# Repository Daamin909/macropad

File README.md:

# Daamin's ShrekPad

### Inspiration

I wanted to boost my productivity and add an aesthetic looking device to my desk setup.

### Challenges

Believe it or not, this was my first time using Fusion 360! I spammed ChatGPT and #hackpad with queries. It also took me a lotta time making the PCB and routing it 😭. I had to reroute a hundred times.

### Case

The case features a very hot Orange and Black look with the keycaps being black and Knob being orange too.

Branding: There is a "Shrek" engraving on both the bottom and middle plate. The top case features an engraving of Shrek's face.

Thickness

- Top: 7mm
- Middle: 1.5mm
- Bottom: 11.5mm
- **Total:** 20mm

### Specifications

BOM:

- 11x Blank DSA Keycaps (11x Black)
- 11x Cherry MX Switches
- 12x 1N4148 diodes
- 1x XIAO RP2040
- 4x M3x20 Bolt ([not available at HQ? if not, then buy from here.](https://amzn.in/d/27J4X2p))
- 4x M3 Nuts
- 4x M3 Heatset
- 1x SSD1306 128x32 0.91" OLED (5V VCC, 3.3V logic, I2C)
- 1x EC11 Rotary Encoder
- 1x Rotary Encoder Knob
- 1x PCB (Please choose "Black" color while ordering 🙃)
- 1x Case (I would like both the TOP and MIDDLE to be printed in Orange and BOTTOM in Black, if not available: Message me @Daamin on Slack)

Others:

- KMK Firmware
- TOP.step
- MIDDLE.step
- BOTTOM.step

|           Schematic            |           PCB            |            Case            |
| :----------------------------: | :----------------------: | :------------------------: |
|  |  |  |

Notes:
Top and Middle printed in Orange, Bottom with Black.
PCB Color has to be black too.

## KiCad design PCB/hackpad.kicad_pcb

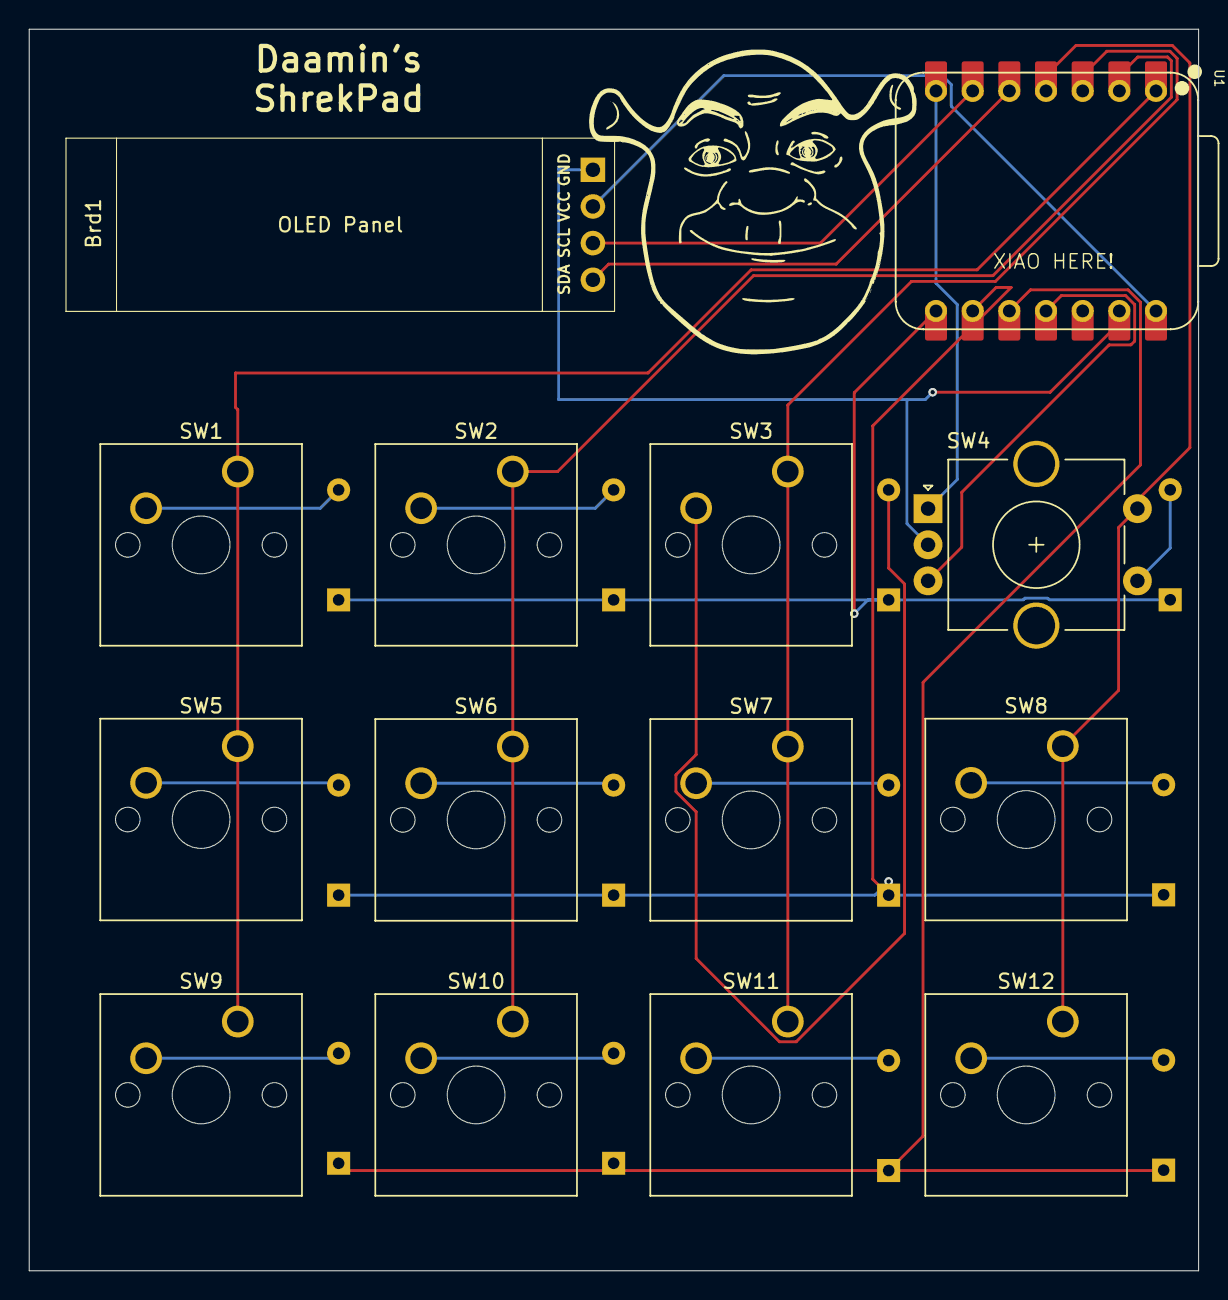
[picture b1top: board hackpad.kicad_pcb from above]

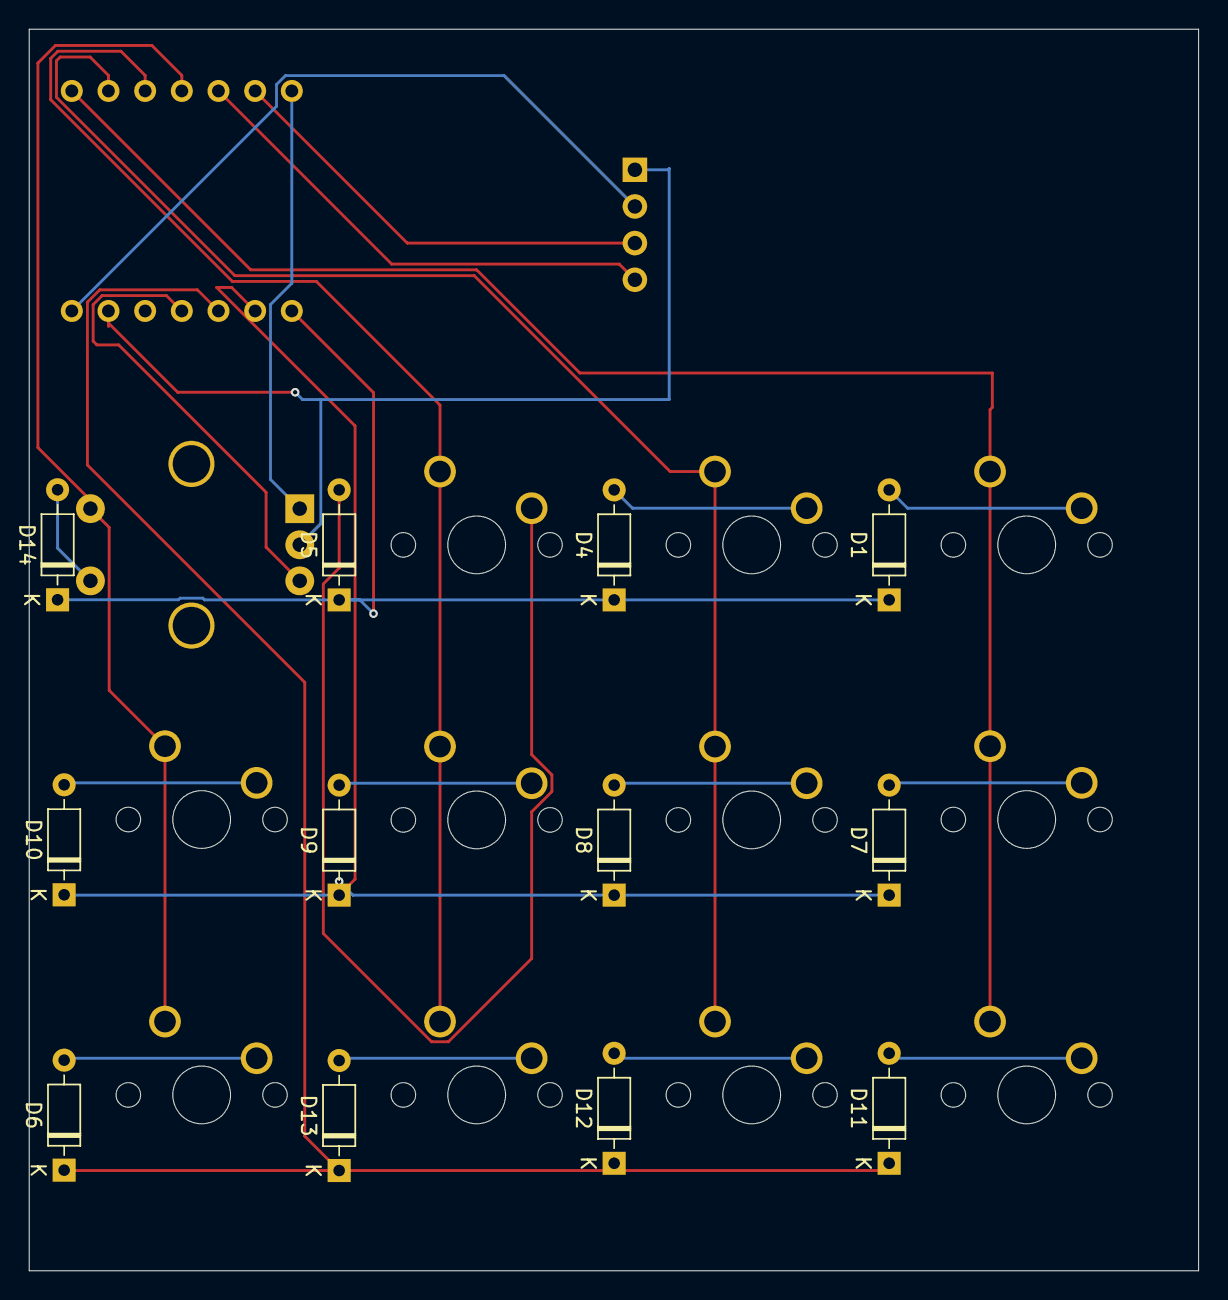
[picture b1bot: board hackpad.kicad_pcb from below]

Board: 2 copper layers, 81.0 x 86.0 mm, 26 parts (12 on the bottom side), 25 nets.

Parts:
Brd1: SSD1306; 128x64OLED
D1, D4, D5, D6, D7, D8, D9, D10, D11, D12, D13, D14: 1N4148; D_DO-35_SOD27_P7.62mm_Horizontal
SW1, SW2, SW3, SW5, SW6, SW7, SW8, SW9, SW10, SW11, SW12: SW_Push; SW_Cherry_MX_1.00u_PCB
SW4: RotaryEncoder_Switch; RotaryEncoder_Alps_EC11E-Switch_Vertical_H20mm_CircularMoun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
U1: XIAO-RP2040-DIP

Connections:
+5V: Brd1.2 (VCC), U1.14 (VBUS)
GND: Brd1.1 (GND), SW4.C, U1.13 (GND)
unnamed: Brd1.3 (SCL), U1.6 (GPIO7/SCL)
unnamed: Brd1.4 (SDA), U1.5 (GPIO6/SDA)
unnamed: D1.2 (A), SW1.2
unnamed: D4.2 (A), SW2.2
unnamed: D5.2 (A), SW3.2
unnamed: D6.2 (A), SW12.2
unnamed: D7.2 (A), SW5.2
unnamed: D8.2 (A), SW6.2
unnamed: D9.2 (A), SW7.2
unnamed: D10.2 (A), SW8.2
unnamed: D11.2 (A), SW9.2
unnamed: D12.2 (A), SW10.2
unnamed: D13.2 (A), SW11.2
unnamed: D14.2 (A), SW4.S1
unnamed: SW4.A, U1.7 (GPIO0/TX)
unnamed: SW4.B, U1.11 (GPIO3/MOSI)
col1: SW1.1, SW5.1, SW9.1, U1.1 (GPIO26/ADC0/A0)
col2: SW2.1, SW6.1, SW10.1, U1.2 (GPIO27/ADC1/A1)
col3: SW3.1, SW7.1, SW11.1, U1.3 (GPIO28/ADC2/A2)
col4: SW4.S2, SW8.1, SW12.1, U1.4 (GPIO29/ADC3/A3)
row1: D1.1 (K), D4.1 (K), D5.1 (K), D14.1 (K), U1.8 (GPIO1/RX)
row2: D7.1 (K), D8.1 (K), D9.1 (K), D10.1 (K), U1.9 (GPIO2/SCK)
row3: D6.1 (K), D11.1 (K), D12.1 (K), D13.1 (K), U1.10 (GPIO4/MISO)

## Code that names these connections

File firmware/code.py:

# Daamin's macropad firmware
# Rev 1.1
# Copyright 2024
# Licensed under zlib license
import board
import busio

from kmk.kmk_keyboard import KMKKeyboard
from kmk.keys import KC
from kmk.scanners import DiodeOrientation
from kmk.modules.macros import Macros, Press, Release, Tap
from kmk.modules.encoder import EncoderHandler
from kmk.extensions.media_keys import MediaKeys
from kmk.modules.mouse_keys import MouseKeys


ROTA = board.D6
ROTB = board.D10
COL1 = board.D0
COL2 = board.D1
COL3 = board.D2
COL4 = board.D3
ROW1 = board.D9
ROW2 = board.D8
ROW3 = board.D7


keyboard = KMKKeyboard()

encoder_handler = EncoderHandler()
keyboard.modules.append(MediaKeys())
keyboard.modules.append(MouseKeys())
encoder_handler.pins = ((ROTA, ROTB, None),)
encoder_handler.map = [((KC.VOLU, KC.VOLD),), ]  

macros = Macros()
keyboard.modules.append(macros)
keyboard.modules.append(encoder_handler)


keyboard.col_pins = (COL1, COL2, COL3, COL4)
keyboard.row_pins = (ROW1, ROW2, ROW3)
keyboard.diode_orientation = DiodeOrientation.COL2ROW


OPEN_VSC = KC.MACRO(Press(KC.LGUI), Tap(KC.SPACE), Release(KC.LGUI), "vsc", Tap(KC.ENTER))
OPEN_SPOTIFY = KC.MACRO(Press(KC.LGUI), Tap(KC.SPACE), Release(KC.LGUI), "spotify", Tap(KC.ENTER))
OPEN_BRAVE = KC.MACRO(Press(KC.LGUI), Tap(KC.SPACE), Release(KC.LGUI), "brave", Tap(KC.ENTER))
OPEN_DISCORD = KC.MACRO(Press(KC.LGUI), Tap(KC.SPACE), Release(KC.LGUI), "discord", Tap(KC.ENTER))
MISSION_CTRL = KC.MACRO(
    Press(KC.LALT),
    Press(KC.LSHIFT),
    Tap(KC.M),
    Release(KC.LSHIFT),
    Release(KC.LALT),
)
keyboard.keymap = [
    [KC.MRWD, KC.MFFD, KC.MW_UP, KC.LGUI(KC.V), OPEN_BRAVE, MISSION_CTRL, KC.MW_DN, KC.LGUI(KC.C), OPEN_VSC, OPEN_SPOTIFY, OPEN_DISCORD, KC.MPLY]
]

if __name__ == '__main__':
    keyboard.go()

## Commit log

2025-02-19 Added Case 3D Model, PCB and Schematic
2025-03-07 add top case to hackpad
2025-03-21 improved tolerances, recompile CAD
2025-03-22 added STL files
2025-05-27 minor via placement change
2025-06-23 updated firmware
2025-06-23 made final changes
2025-06-23 added no storage thingy
